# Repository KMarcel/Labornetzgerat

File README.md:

# Labornetzgerat
Dies ist unser Abschluss Schulprojekt. Es handelt sich um ein Labornetzgerät mit einer Digitalen eingabe per Keypad und einer digitalen Ausgabe per LCD

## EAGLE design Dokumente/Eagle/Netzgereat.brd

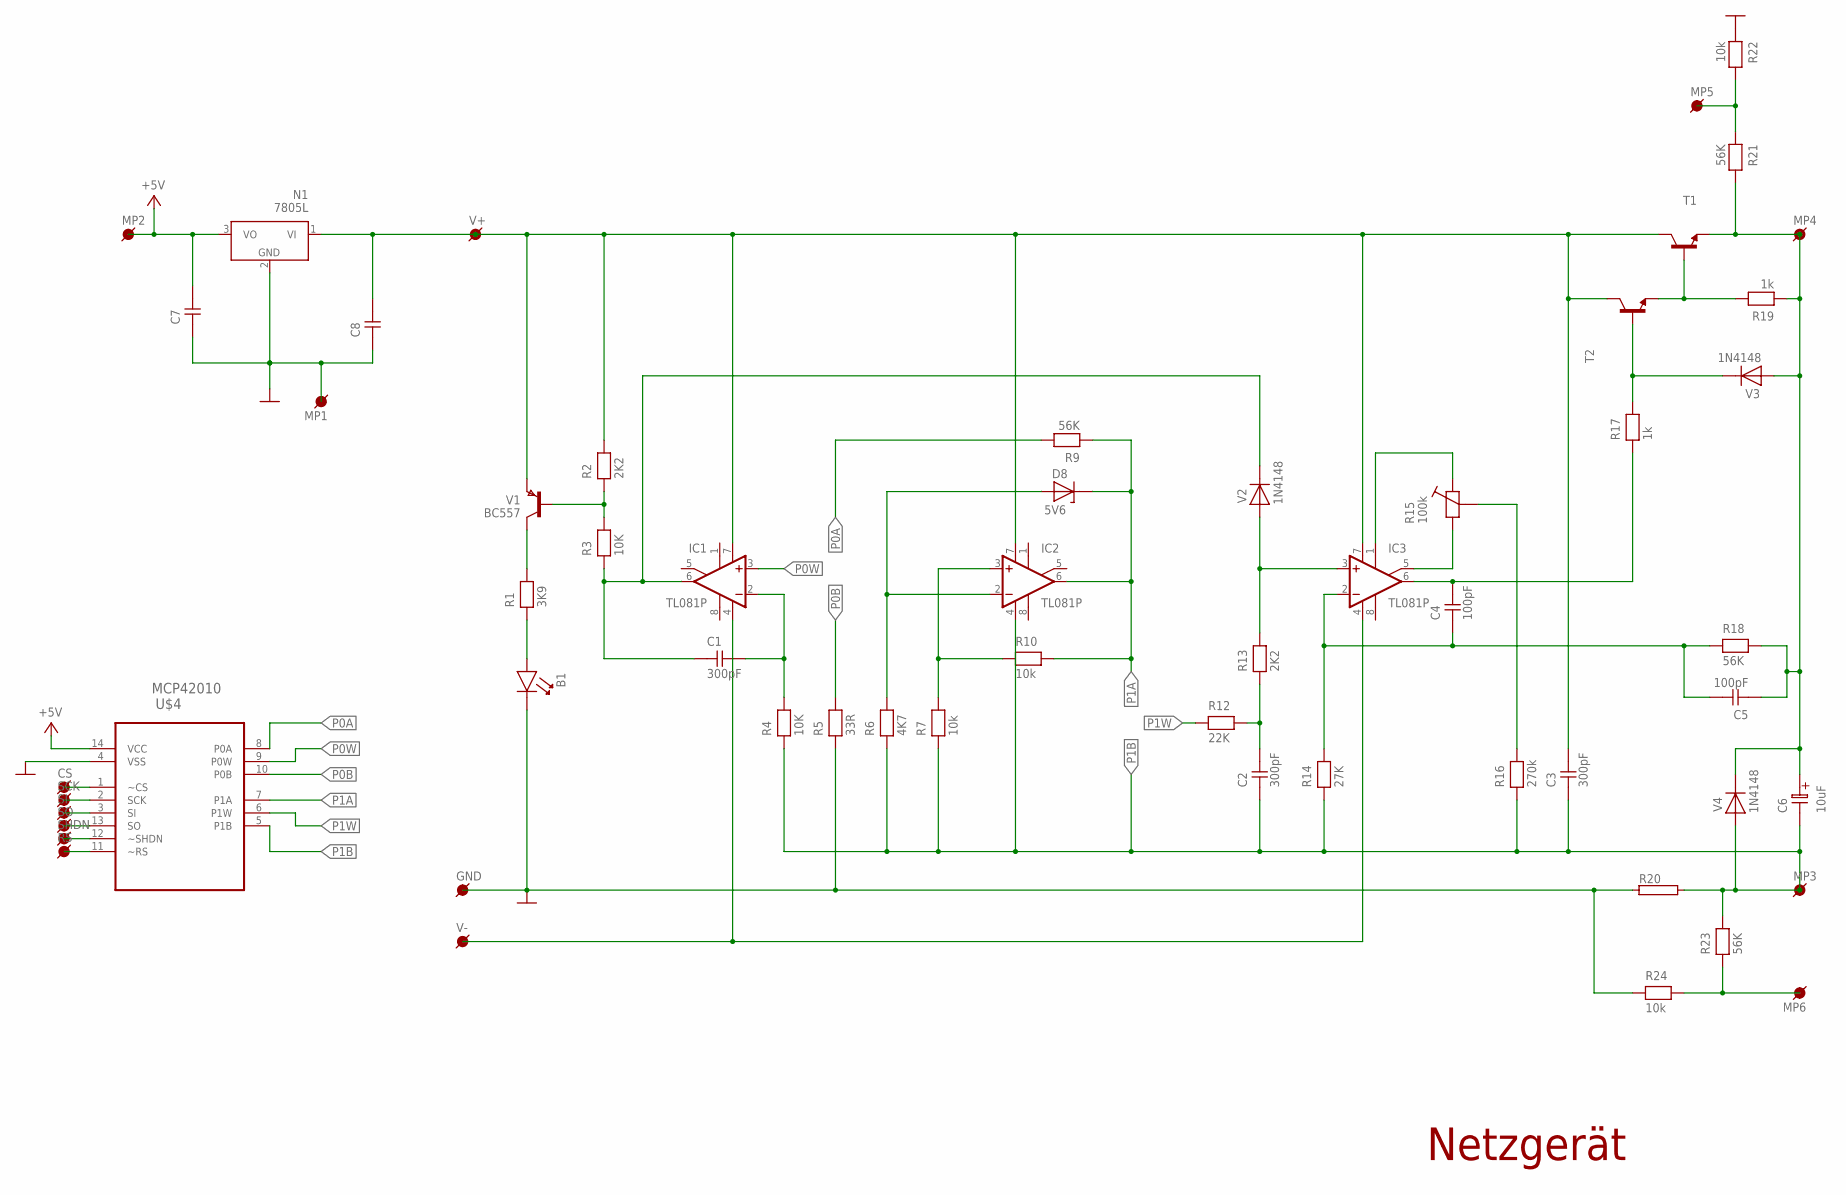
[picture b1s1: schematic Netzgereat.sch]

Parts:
B1: LED
C1, C2, C3: 300pF; C-5
C4, C5: 100pF; C-5
C6: 10uF; ES-5
C7, C8: C-5
CS: MP
D8: 5V6; D-7,5
GND: MP
IC1, IC2, IC3: TL081P; DIL08
MP1, MP2, MP3, MP4, MP5, MP6: MP
N1: 7805L; T0-92C
R1: 3K9; R-10
R2, R13: 2K2; R-10
R3, R4: 10K; R-10
R5: 33R; R-10
R6: 4K7; R-10
R7, R10, R22, R24: 10k; R-10
R9, R18, R21, R23: 56K; R-10
R12: 22K; R-10
R14: 27K; R-10
R15: 100k; PT-SPIN
R16: 270k; R-10
R17, R19: 1k; R-10
R20: RKH208-8; KH208-8
RS: MP
SCK: MP
SHDN: MP
SI: MP
SO: MP
T1: -NPN-TOP3V; TOP3V
T2: -NPN-TO126V; TO126V
U$4: MCP42010
V1: BC557; TO-92C
V2, V4: 1N4148; D-5
V3: 1N4148; D-7,5
V+: MP
V-: MP

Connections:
+5V: C7.2, MP2.P$1, N1.3 (VO), U$4.14 (VCC)
GND: B1.2 (K), C7.1, C8.1, GND.P$1, MP1.P$1, N1.2 (GND), R5.1, R20.1, R22.1, R24.1, U$4.4 (VSS)
unnamed: B1.1 (A), R1.1
unnamed: R1.2, V1.3 (C)
unnamed: C1.1, IC1.6 (OUT), R3.1, V2.2 (K)
unnamed: C3.2, C8.2, IC1.7 (V+), IC2.7 (V+), IC3.7 (V+), N1.1 (VI), R2.2, T1.C, T2.2 (C), V1.1 (E), V+.P$1
unnamed: R2.1, R3.2, V1.2 (B)
unnamed: C1.2, IC1.2 (-IN), R4.2
unnamed: IC1.4 (V-), IC3.4 (V-), V-.P$1
unnamed: MP5.P$1, R21.1, R22.2
unnamed: IC2.3 (+IN), R7.2, R10.1
unnamed: D8.1 (A), IC2.2 (-IN), R6.2
unnamed: CS.P$1, U$4.1 (~CS)
unnamed: SCK.P$1, U$4.2 (SCK)
unnamed: SI.P$1, U$4.3 (SI)
unnamed: C2.2, R12.2, R13.1
unnamed: IC3.3 (+IN), R13.2, V2.1 (A)
unnamed: C4.1, C5.2, IC3.2 (-IN), R14.2, R18.1
unnamed: IC3.1 (ON1), R15.3
unnamed: IC3.5 (ON2), R15.1
unnamed: R15.2, R16.2
unnamed: C4.2, IC3.6 (OUT), R17.1
unnamed: SO.P$1, U$4.13 (SO)
unnamed: R17.2, T2.3 (B), V3.2 (K)
unnamed: SHDN.P$1, U$4.12 (~SHDN)
unnamed: C5.1, C6.1, MP4.P$1, R18.2, R19.1, R21.2, T1.E, V3.1 (A), V4.2 (K)
unnamed: RS.P$1, U$4.11 (~RS)
unnamed: R19.2, T1.B, T2.1 (E)
unnamed: MP6.P$1, R23.1, R24.2
P0A: R9.2, U$4.8 (P0A)
P0B: R5.2, U$4.10 (P0B)
P0W: IC1.3 (+IN), U$4.9 (P0W)
P1A: D8.2 (K), IC2.6 (OUT), R9.1, R10.2, U$4.7 (P1A)
P1B: C2.1, C3.1, C6.2, IC2.4 (V-), MP3.P$1, R4.1, R6.1, R7.1, R14.1, R16.1, R20.2, R23.2, U$4.5 (P1B), V4.1 (A)
P1W: R12.1, U$4.6 (P1W)

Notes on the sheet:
Netzgerät

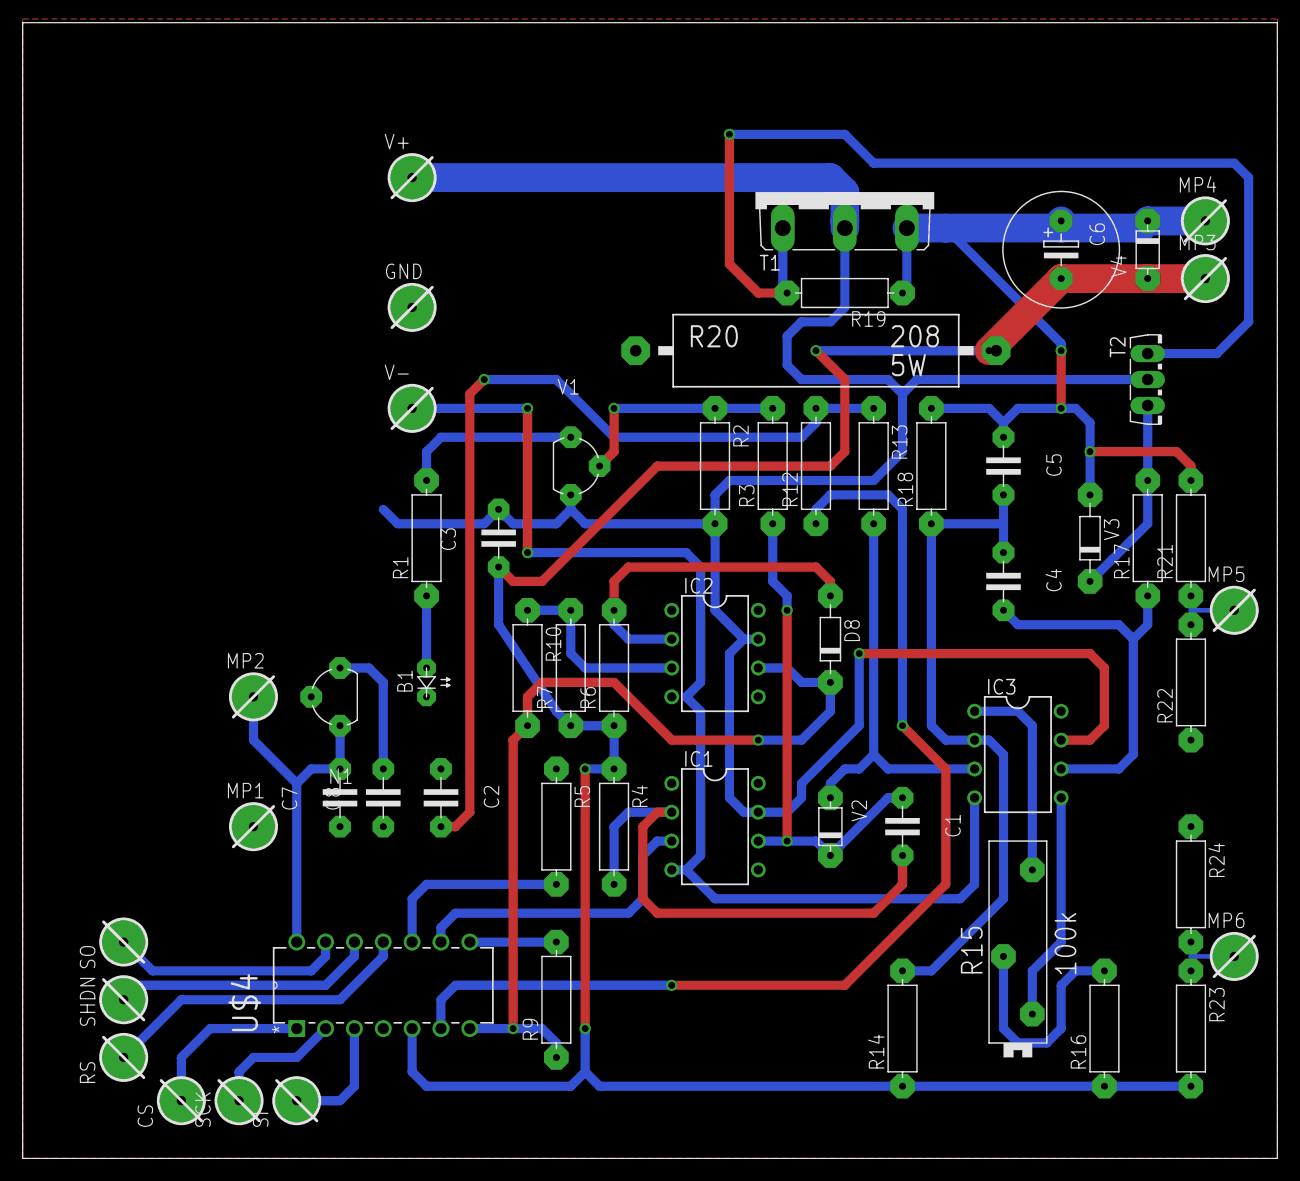
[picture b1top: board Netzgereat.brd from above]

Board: 2 copper layers, 110.5 x 100.0 mm, 58 parts (0 on the bottom side), 35 nets.

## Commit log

2017-06-19 Create I
2017-06-19 Create 1
2017-06-19 Rename i to README.md
